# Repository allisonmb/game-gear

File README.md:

# Production Release - Game Gear
Our project was focused on recreating the original experience of the SEGA Game Gear handheld console with modern hardware and improved functionality.

[Build Instructions](Build%20Instructions.pdf)

[Bill of Materials](Bill%20of%20Materials.pdf)

[Raspberry Pi Image](https://drive.google.com/drive/u/0/folders/1cTOPLiqQtfveVBptVOEDtFShPZntb5K-)

Each aspect of the project is linked below, with README files indicating their functionality, how to run them, and known bugs.
- [Emulator ROM Implementation](romDev/)
- [Cartridge Auto Launch Scripts](romDev/udev_scripts/)
- [PCB Designs](https://github.com/allisonmb/game-gear/tree/17-pcb/pcbDesign)
- [GPIOnext](https://github.com/mholgatem/GPIOnext) - Used for interfacing with buttons through GPIO
- [3D Model](https://drive.google.com/file/d/1HNF1D_YHym1qWQATkMjLh69oOEiKL8Yn/view?usp=sharing) - Will need blender to view

Below are links to parts of the project that are no longer in development
- [FPGA Implementation](A-Z80/)
- [Z80 Assembly Test Code](<z80 assembly/>)

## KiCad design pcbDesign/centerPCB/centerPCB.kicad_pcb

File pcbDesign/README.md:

# PCB Design and Schematics
There are 3 PCBs: the left, right, and center PCBs. These are connected to eachother with header pins. Note: The "main PCB" is an old version which was before the PCB was split into 3. "GG PCB" is a remake of the original Game Gear PCB from https://oshwlab.com/maarten040476_3348/sega-game-gear-837-7996.
## Currently Implemented
### Center PCB
The center PCB connects to the left and right PCBs. 
The center PCB contains:
- [Raspberry Pi Zero W](https://www.raspberrypi.com/products/raspberry-pi-zero-w/)
- [3.5 Waveshare HDMI Screen](https://www.waveshare.com/wiki/3.5inch_HDMI_LCD)

### Left PCB
The left PCB contains:
- D-Pad buttons - These are traces on the board that are not connected. They are connected by a metal disk attached to the button that completes the circuit when the button is pushed.
- Power LED - A 3mm red LED with a 270 ohm resistor.

### Right PCB
The right PCB contains:
 - Start, 1, and 2 buttons - Works the same as the D-Pad buttons

## To be Implemented
### Center PCB
- Batery PCB - Need to decide on exact battery and battery board that will provide enough power for the other components

### Left PCB
- Volume Dial - Connected to rotary encoder that can be interpreted by the Raspberry Pi to change the system's volume level.
- Audio Amplifier - Connected to the Raspberry Pi and is capable of converting digital sound to anologue to go to a speaker. Currently looking at using [MAX98357A](https://www.adafruit.com/product/3006)

### Right PCB
The right PCB contains:
 - Brightness Dial - Same implementation as the volume dial, except for the screen brightness

## Current Issues
- The PCB is not complete, the parts listed above need to be added
- There may be an issue with using the MAX98357 audio amplifier with the PiJuice. Both use i2c for communication with the Raspberry Pi. However, they use different pins to do so and thus both may work together.
- The battery must be large enough to support the Raspberry Pi and the HDMI screen. The power consumption for both needs to be measured to choose a big enough battery.
- The largest single cell battery that can fit in the current case is 1200mAh. It is unlikely this is sufficient to power the console. There are two possible fixes for this. The case can be altered to allow a larger signle cell battery to fit, but this would cause issues with holding the console. Or multiple batteries in series could be used, but this would eliminate use of some battery PCBs which only work with single cell batteries.

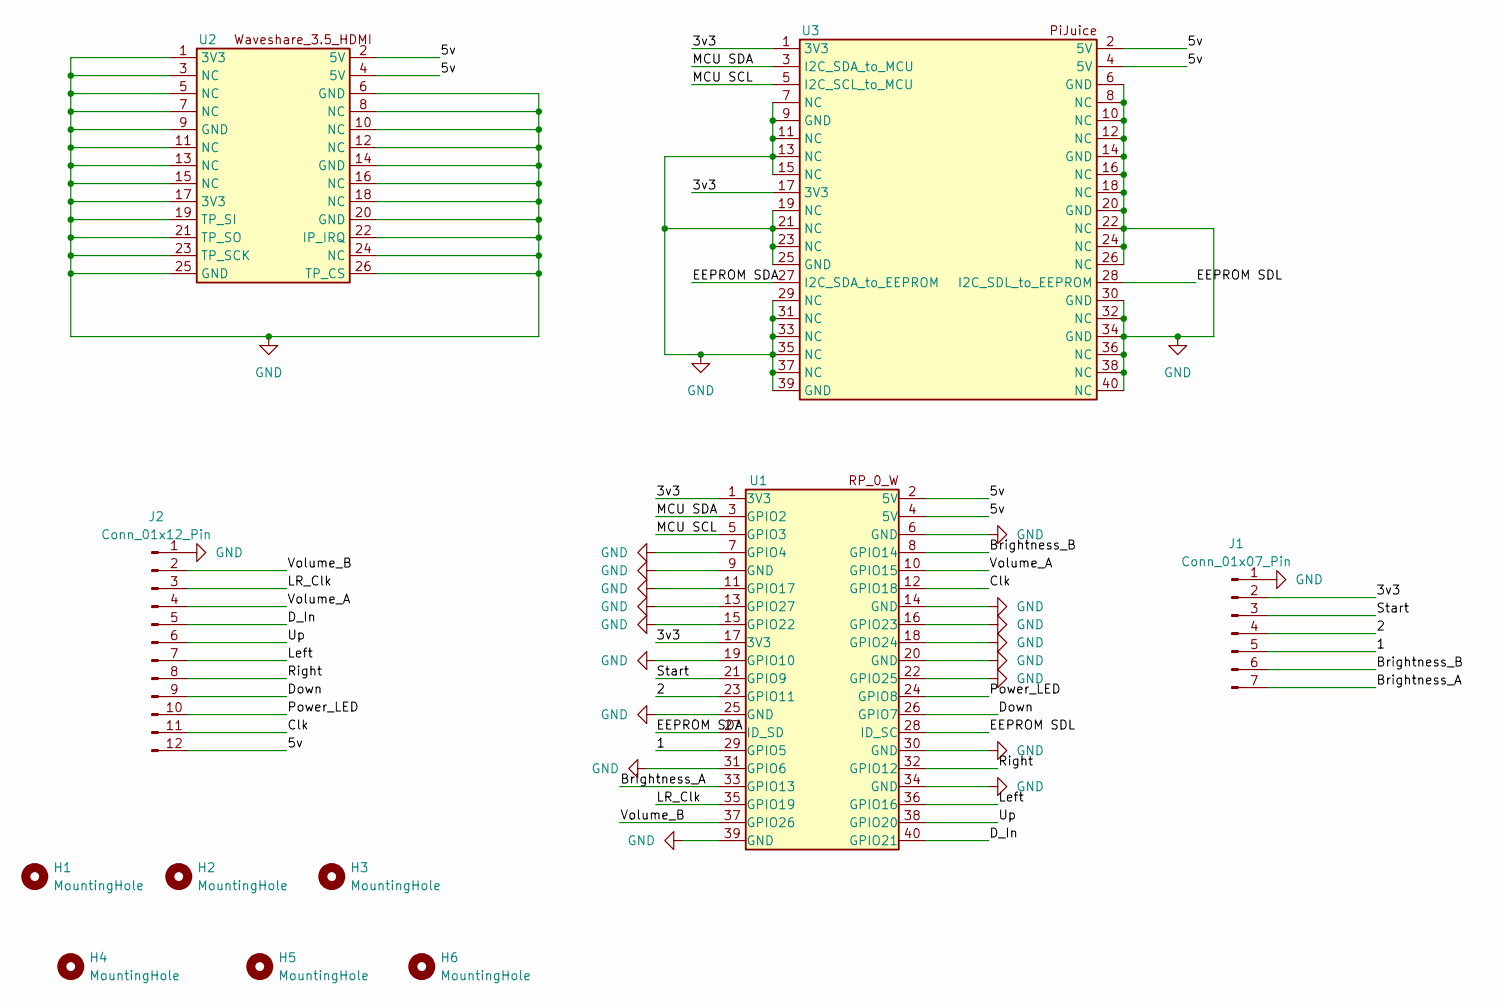
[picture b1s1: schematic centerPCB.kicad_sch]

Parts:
H1, H2, H3: MountingHole; MountingHole_2.1mm
H4, H5, H6: MountingHole; MountingHole_2.5mm
J1: Conn_01x07_Pin; PinHeader_1x07_P2.54mm_Vertical
J2: Conn_01x12_Pin; PinHeader_1x12_P2.54mm_Vertical
U1, U3: PinHeader_2x20_P2.54mm_Vertical
U2: PinHeader_2x13_P2.54mm_Vertical

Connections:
/1: J1.5, U1.29 (GPIO5)
/2: J1.4, U1.23 (GPIO11)
/3v3: J1.2, U1.1 (3V3), U1.17 (3V3), U3.1 (3V3), U3.17 (3V3)
/5v: J2.12, U1.2 (5V), U1.4 (5V), U2.2 (5V), U2.4 (5V), U3.2 (5V), U3.4 (5V)
/Brightness_A: J1.7, U1.33 (GPIO13)
/Brightness_B: J1.6, U1.8 (GPIO14)
/Clk: J2.11, U1.12 (GPIO18)
/D_In: J2.5, U1.40 (GPIO21)
/Down: J2.9, U1.26 (GPIO7)
/EEPROM SDA: U1.27 (ID_SD), U3.27 (I2C_SDA_to_EEPROM)
/EEPROM SDL: U1.28 (ID_SC), U3.28 (I2C_SDL_to_EEPROM)
/LR_Clk: J2.3, U1.35 (GPIO19)
/Left: J2.7, U1.36 (GPIO16)
/MCU SCL: U1.5 (GPIO3), U3.5 (I2C_SCL_to_MCU)
/MCU SDA: U1.3 (GPIO2), U3.3 (I2C_SDA_to_MCU)
/Power_LED: J2.10, U1.24 (GPIO8)
/Right: J2.8, U1.32 (GPIO12)
/Start: J1.3, U1.21 (GPIO9)
/Up: J2.6, U1.38 (GPIO20)
/Volume_A: J2.4, U1.10 (GPIO15)
/Volume_B: J2.2, U1.37 (GPIO26)
GND: J1.1, J2.1, U1.6 (GND), U1.7 (GPIO4), U1.9 (GND), U1.11 (GPIO17), U1.13 (GPIO27), U1.14 (GND), U1.15 (GPIO22), U1.16 (GPIO23), U1.18 (GPIO24), U1.19 (GPIO10), U1.20 (GND), U1.22 (GPIO25), U1.25 (GND), U1.30 (GND), U1.31 (GPIO6), U1.34 (GND), U1.39 (GND), U2.1 (3V3), U2.3 (NC), U2.5 (NC), U2.6 (GND), U2.7 (NC), U2.8 (NC), U2.9 (GND), U2.10 (NC), U2.11 (NC), U2.12 (NC), U2.13 (NC), U2.14 (GND), U2.15 (NC), U2.16 (NC), U2.17 (3V3), U2.18 (NC), U2.19 (TP_SI), U2.20 (GND), U2.21 (TP_SO), U2.22 (IP_IRQ), U2.23 (TP_SCK), U2.24 (NC), U2.25 (GND), U2.26 (TP_CS), U3.6 (GND), U3.7 (NC), U3.8 (NC), U3.9 (GND), U3.10 (NC), U3.11 (NC), U3.12 (NC), U3.13 (NC), U3.14 (GND), U3.15 (NC), U3.16 (NC), U3.18 (NC), U3.19 (NC), U3.20 (GND), U3.21 (NC), U3.22 (NC), U3.23 (NC), U3.24 (NC), U3.25 (GND), U3.26 (NC), U3.29 (NC), U3.30 (GND), U3.31 (NC), U3.32 (NC), U3.33 (NC), U3.34 (GND), U3.35 (NC), U3.36 (NC), U3.37 (NC), U3.38 (NC), U3.39 (GND), U3.40 (NC)

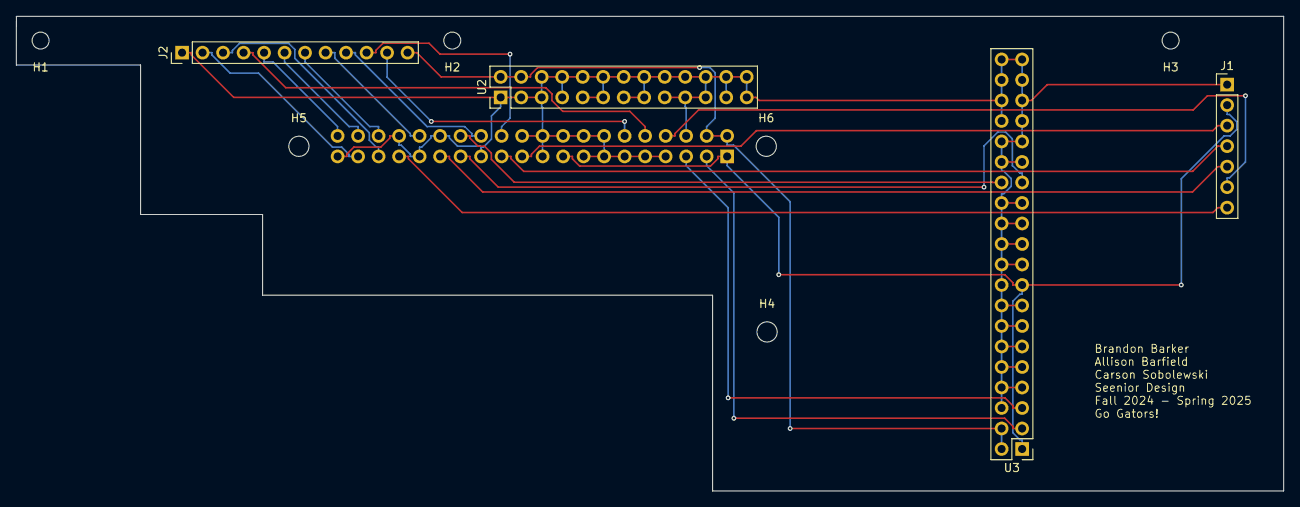
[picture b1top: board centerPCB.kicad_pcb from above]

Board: 2 copper layers, 157.0 x 58.8 mm, 11 parts (1 on the bottom side), 22 nets.

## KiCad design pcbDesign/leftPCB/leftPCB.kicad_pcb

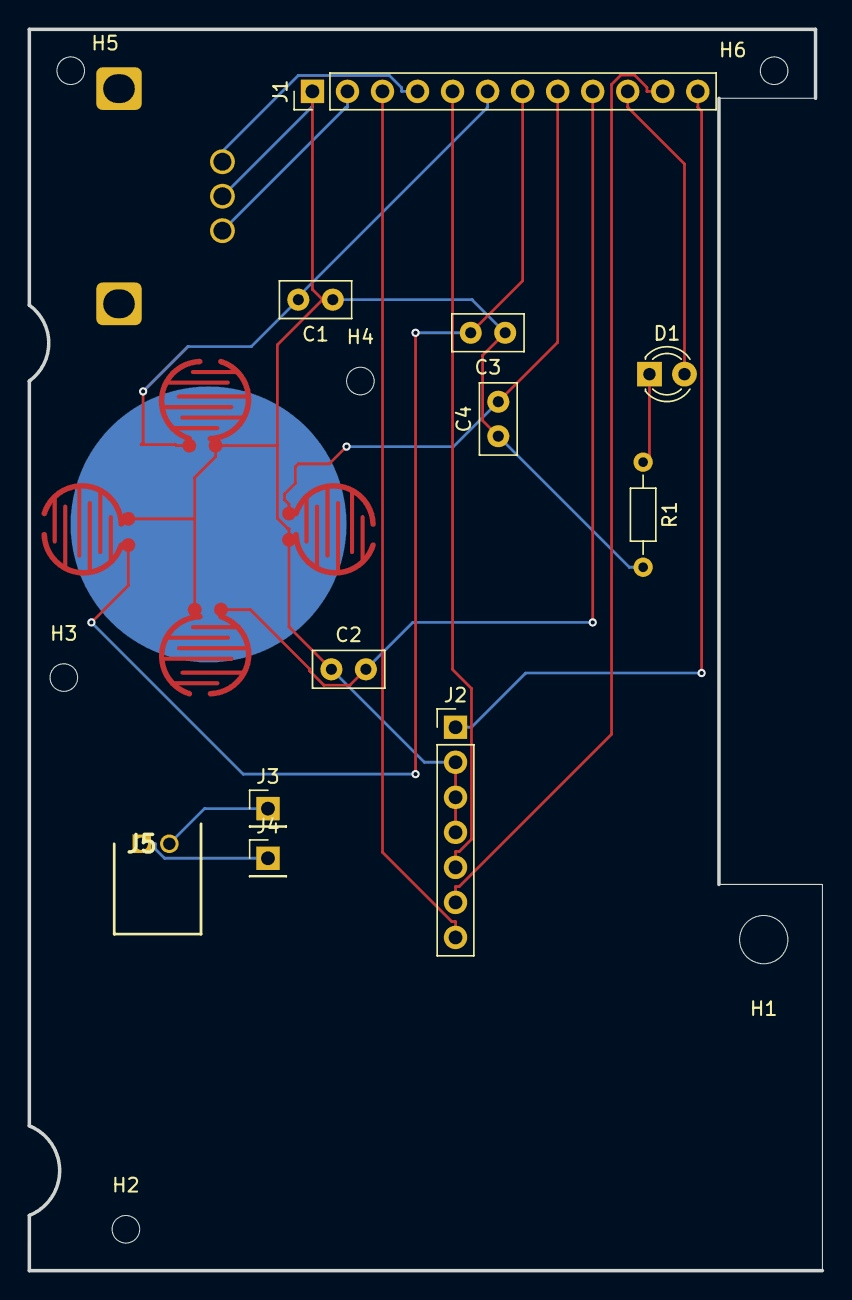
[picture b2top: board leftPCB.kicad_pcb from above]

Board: 2 copper layers, 57.5 x 90.0 mm, 22 parts (1 on the bottom side), 15 nets.

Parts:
C1, C2, C3, C4: 1u; C_Disc_D5.0mm_W2.5mm_P2.50mm
D1: LED; LED_D3.0mm
H1: MountingHole; MountingHole_3.5mm
H2, H3, H4, H5, H6: MountingHole; MountingHole_2mm
J1: Conn_01x12_Pin; PinHeader_1x12_P2.54mm_Vertical
J2: Conn_01x07_Pin; PinHeader_1x07_P2.54mm_Vertical
J3, J4: Conn_01x01_Pin; PinHeader_1x01_P2.54mm_Vertical
J5: 440055-2; SHDRRA2W50P0X200_1X2_600X770X525P
R1: R; R_Axial_DIN0204_L3.6mm_D1.6mm_P7.62mm_Horizontal
SW1: UP; BUTTON
SW2: DOWN; BUTTON
SW3: LEFT; BUTTON
SW4: RIGHT; BUTTON
SW5: RotaryEncoder; PES12

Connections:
/5v: J1.12, J2.1
/Clk: J1.11, J2.6
/D_In: J1.5, J2.5
/Down: C2.2, J1.9, SW2.2
/LR_Clk: J1.3, J2.7
/Left: C3.2, J1.7, SW3.2
/Power_LED: D1.2 (A), J1.10
/Right: C4.2, J1.8, SW4.2
/Speaker_Neg: J4.1, J5.1
/Speaker_Pos: J3.1, J5.2
/Up: C1.2, J1.6, SW1.2
/Volume_A: J1.4, SW5.A
/Volume_B: J1.2, SW5.B
GND: C1.1, C2.1, C3.1, C4.1, J1.1, J2.2, J2.3, J2.4, R1.2, SW1.1, SW2.1, SW3.1, SW4.1, SW5.C
unnamed: D1.1 (K), R1.1

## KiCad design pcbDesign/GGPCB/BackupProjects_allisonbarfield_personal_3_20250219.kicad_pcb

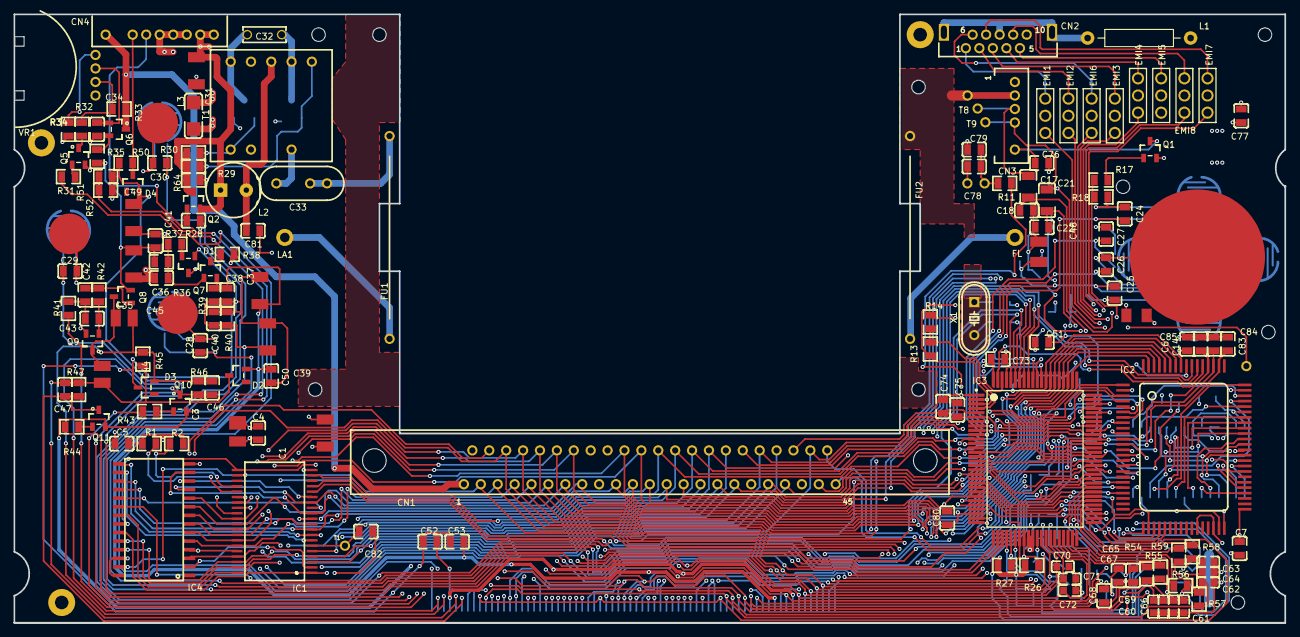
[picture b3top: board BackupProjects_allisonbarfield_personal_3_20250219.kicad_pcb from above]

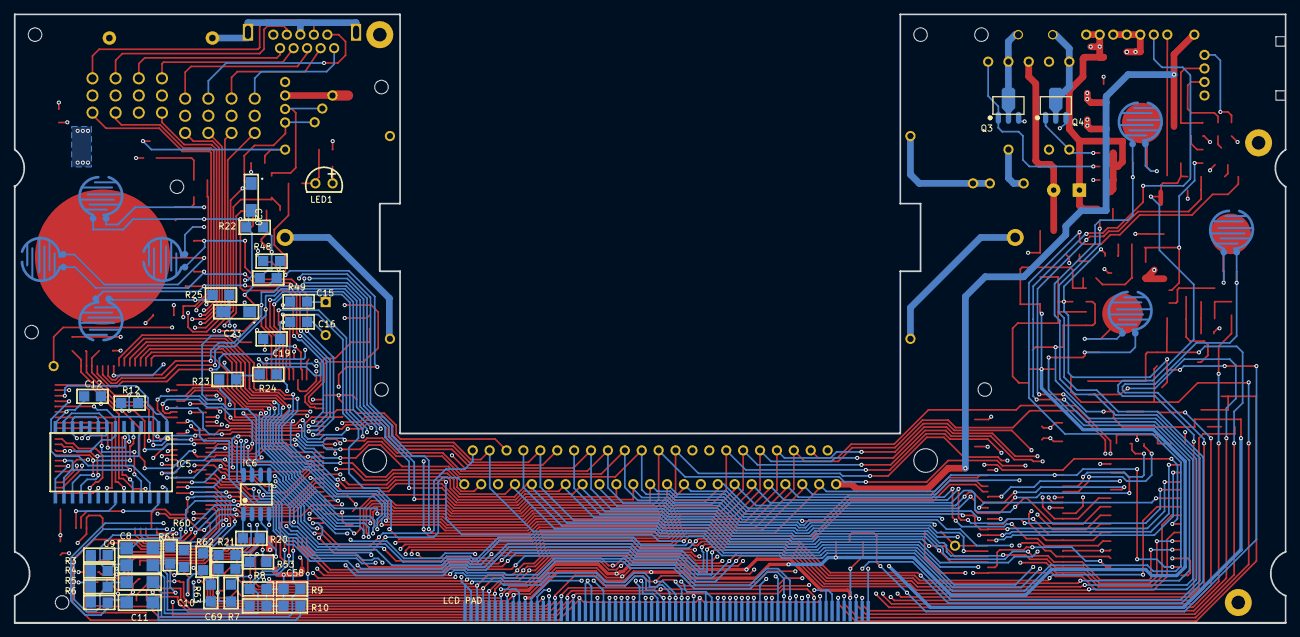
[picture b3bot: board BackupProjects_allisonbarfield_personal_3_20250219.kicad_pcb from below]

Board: 4 copper layers, 188.0 x 90.0 mm, 208 parts (47 on the bottom side), 196 nets.

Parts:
C1, C3, C6, C31, C35, C37, C39, C44, C45, C48, C49: 1u; CAPASITOR TEST
C4, C5, C7, C14, C18, C22, C24, C25, C26, C27, C28, C29, C30, C34, C36, C38, C40, C41, C42, C43, C46, C47, C50, C51, C52, C53, C65, C67, C68, C73, C74, C75, C76, C77, C78, C79, C80, C81, C82, C83, C84, C85: 1u; C0805
C8, C9, C10, C11: 1u; 1806
C12, C15, C16, C19, C58, C69: 1u; C1205
C17, C21: 1u; C1206
C20, C23: 1u; C20,23
C32: 1u; CERAMIC-5.08
C33: 1u; CAP33
C59, C60, C61, C62, C63, C64, C66, C70, C71, C72: 1u; C0603
CN1: CONN 45P FOR GG 01; CN1
CN2: CONN 10P FOR GG; CN2
CN3: WIRE HARN SP FOR GG; CONNECTOR3
CN4: CN4
D1, D2, D4: 1SS184; SOT-23-3_L2.9-W1.3-P1.90-LS2.4-TR
D3: 1SS184; TO-236MOD_L2.9-W1.5-P0.95-LS2.5-BR
EMI1, EMI2, EMI3, EMI4, EMI5, EMI6, EMI7, EMI8: EMI; FILTER-TH_3P-L8.0-W2.5-P2.54-R
FU1, FU2: Glass tube fuse2A 3F 250VAC; FUSE
Hole_gge24781: Hole_gge24781
Hole_gge24790: Hole_gge24790
Hole_gge24795: Hole_gge24795
Hole_gge24800: Hole_gge24800
Hole_gge24805: Hole_gge24805
Hole_gge24816: Hole_gge24816
Hole_gge24821: Hole_gge24821
Hole_gge24826: Hole_gge24826
Hole_gge24831: Hole_gge24831
IC1: TMPZ84C00AM-6; SSOP-40
IC2: 315-5377; 80-QFP
IC3: 315-5378B; 100QFP
IC4: MB8464A-10LL; FP-28DA
IC5: HM65256BLFP-10T; FP-28DA
IC6: IC6; KM 8SOP 5X6
L1: 1m; CHOKE_HORIZONTAL_RM15MM
L2: 1m; 100UH-3A
L3: 1m; L1806
LA1: Lamp; LAMP
LED1: LED; LED-TH_2P-L4.80-W3.80-P2.54-L
Pad_gge24769: Pad_gge24769
Pad_gge24780: Pad_gge24780
Pad_gge24811: Pad_gge24811
Pad_gge85411: Pad_gge85411
Pad_gge90736: Pad_gge90736
Pad_gge109066: Pad_gge109066
Pad_gge109074: Pad_gge109074
Pad_gge109081: Pad_gge109081
Q1, Q7: 2SC1623; SOT-23-3_L2.9-W1.3-P1.90-LS2.4-TR
Q2: 2SC1623???; SOT-23-3_L2.9-W1.3-P1.90-LS2.4-TR
Q3, Q4: 2sd1614; SOT89-3L
Q5, Q6, Q9, Q11: 2SC1623; SOT-23-3_L2.9-W1.3-P1.90-LS2.4-L
Q8: 2SA812; SOT-23-3_L2.9-W1.3-P1.90-LS2.4-TR
Q10: 2SA812; SOT-23-3_L2.9-W1.3-P1.90-LS2.4-L
R1, R2, R11, R13, R14, R17, R18, R26, R27, R30, R31, R32, R33, R34, R35, R36, R37, R38, R39, R40, R41, R42, R43, R44, R45, R46, R47, R50, R51, R52, R54, R55, R56, R57, R58, R59, R64: 0; R0805
R3, R4, R5, R6, R7, R8, R9, R10, R12, R20, R21, R22, R23, R24, R25, R48, R49, R53, R60, R61, R62, R63: 0; R1205
R28, R29: 0; C0805
SW1: UP; BUTTON
SW2: DOWN; BUTTON
SW3: LEFT; BUTTON
SW4: RIGHT; BUTTON
SW5: TL; BUTTON
SW6: TR; BUTTON
SW7: PS; BUTTON
T1: Transformer T1; TR1
U1: LCD PAD; LCD
VR1: 20K; VR1
X1: 32.2159MHz; HC-49US_L11.5-W4.5-P4.88

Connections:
+2.5V: C48.1, R7.1, R8.1, R9.1, R10.1, R26.1, R27.2, R48.2, R49.1
+5V: C1.1, C3.1, C4.1, C5.1, C6.1, C7.1, C12.1, C14.1, C31.1, C51.1, C77.2, C78.2, C80.1, CN1.2, CN1.35, CN4.1, CN4.2, EMI5.1, IC1.11, IC2.2, IC2.12, IC2.41, IC3.2, IC3.24, IC3.29, IC3.52, IC3.79, IC4.26, IC4.28, IC5.28, L2.1, L3.1, LED1.1, Q2.1, Q2.3, R1.1, R2.1, R12.2, R29.1, R30.1, R38.2, R64.2, U1.10, U1.30, U1.50
+34V: CN1.1, CN4.9, Q6.1, R33.2
A0: CN1.12, IC1.30, IC2.69, IC3.99, IC4.10
A1: CN1.11, IC1.31, IC3.98, IC4.9
A2: CN1.10, IC1.32, IC3.97, IC4.8
A3: CN1.9, IC1.33, IC3.96, IC4.7
A4: CN1.8, IC1.34, IC3.95, IC4.6
A5: CN1.7, IC1.35, IC3.94, IC4.5
A6: CN1.6, IC1.36, IC2.70, IC3.93, IC4.4
A7: CN1.5, IC1.37, IC2.71, IC3.92, IC4.3
A8: CN1.31, IC1.38, IC3.91, IC4.25
A9: CN1.30, IC1.39, IC3.90, IC4.24
A10: CN1.25, IC1.40, IC3.89, IC4.21
A11: CN1.29, IC1.1, IC4.23
A12: CN1.4, IC1.2, IC4.2
A13: CN1.32, IC1.3
A14: CN1.33, IC1.4, IC2.3
A15: CN1.28, IC1.5, IC2.4
AD0: IC2.45, IC5.10, IC5.11
AD1: IC2.46, IC5.9, IC5.12
AD2: IC2.48, IC5.8, IC5.13
AD3: IC2.49, IC5.7, IC5.15
AD4: IC2.50, IC5.6, IC5.16
AD5: IC2.51, IC5.5, IC5.17
AD6: IC2.53, IC5.4, IC5.18
AD7: IC2.54, IC5.19
ANALOG+5V: C19.1, CN3.1, IC6.8, L3.2, R3.2, R4.2, R5.2, R6.2, R48.1
C8_1: C8.1, IC3.36, R7.2
C9_2: C9.2, IC2.14, R4.1
C10_2: C10.2, IC2.15, R5.1
C11_2: C11.2, IC2.16, R6.1
C17_1: C17.1, C18.1, R20.2, R21.2
C21_1: C21.1, C22.2, R23.2, R24.2
C23_2: C23.2, CN1.45, R25.2
C32_1: C32.1, Q4.2, T1.1
C32_2: C32.2, Q3.2, T1.4
C33_1: C33.1, T1.8
C42_2: C42.2, C43.2, R41.1
C44_1: C44.1, C47.2, D2.3, R45.2, R47.2, U1.64
C45_2: C45.2, C46.2, D3.2, R45.1, R46.2, U1.66
C46_1: C46.1, Q10.1, R46.1, U1.67
C73_1: C73.1, IC3.100
CCLK: C74.2, CN1.40, IC3.5
CL2: IC3.46, U1.9, U1.29, U1.49
CLA1: C64.2, R59.2, U1.15
CLA2: C66.2, R61.2, U1.35
CLA3: C68.2, R63.2, U1.55
CLB1: C63.2, R58.2, U1.14
CLB2: C65.2, R60.2, U1.34
CLB3: C67.2, R62.2, U1.54
CLK: C82.2, IC1.6, Pad_gge85411.3
CN3_3: C17.2, CN3.3, Pad_gge109074.6
CN3_4: C21.2, CN3.4, Pad_gge109081.7
CN3_5: C76.1, CN3.5, IC3.25, Q1.3
CN4_6: CN4.6, IC3.30
CN4_7: CN4.7, D4.3, R50.1
D0: CN1.13, IC1.14, IC2.73, IC3.88, IC4.11
D1: CN1.14, IC1.15, IC2.74, IC3.87, IC4.12
D01: C61.2, R56.2, U1.18, U1.38, U1.58
D2: CN1.15, IC1.12, IC2.75, IC3.86, IC4.13
D02: C59.2, R54.2, U1.16, U1.36, U1.56
D3: CN1.19, IC1.8, IC2.76, IC3.85, IC4.15
D03: C62.2, R57.2, U1.19, U1.39, U1.59
D4: CN1.20, IC1.7, IC2.77, IC3.84, IC4.16
D04: C60.2, R55.2, U1.17, U1.37, U1.57
D5: CN1.21, IC1.9, IC2.78, IC3.83, IC4.17
D6: CN1.22, IC1.10, IC2.79, IC3.82, IC4.18
D7: CN1.23, IC1.13, IC2.1, IC3.81, IC4.19
DB: C58.2, R53.2, U1.3, U1.23, U1.43
DOWN: C25.2, IC3.8, SW2.1
DW: IC3.51, U1.20, U1.40, U1.60
EMI1_1: EMI1.1, IC3.72
EMI1_3: CN2.1, EMI1.3
EMI2_1: EMI2.1, IC3.73
EMI2_3: CN2.2, EMI2.3
EMI3_1: EMI3.1, IC3.74
EMI3_3: CN2.3, EMI3.3
EMI4_1: EMI4.1, IC3.75
EMI4_3: CN2.4, EMI4.3
EMI5_3: CN2.5, EMI5.3
EMI6_1: EMI6.1, IC3.76
EMI6_3: CN2.6, EMI6.3
EMI7_1: EMI7.1, IC3.78
EMI7_3: CN2.7, EMI7.3
EMI8_1: EMI8.1, IC3.77
EMI8_3: CN2.9, EMI8.3
EXM1: CN1.34, IC2.6
EXM2: CN1.27, IC2.7
FU1_1: C33.2, FU1.1
FU1_2: FU1.2, LA1.2
GG: CN1.42, IC3.66, R12.1, R31.1
GND: C1.2, C3.2, C4.2, C5.2, C6.2, C7.2, C12.2, C14.2, C15.2, C16.2, C18.2, C19.2, C22.1, C24.1, C25.1, C26.1, C27.1, C28.1, C29.1, C30.1, C31.2, C34.1, C35.2, C36.1, C41.1, C48.2, C49.2, C51.2, C58.1, C59.1, C60.1, C61.1, C62.1, C63.1, C64.1, C65.1, C66.1, C67.1, C68.1, C69.1, C70.1, C71.1, C72.1, C73.2, C74.1, C75.1, C76.2, C77.1, C79.1, C80.2, C81.1, C82.1, C83.2, C84.2, C85.2, CN1.16, CN1.17, CN1.18, CN1.41, CN3.2, CN4.3, CN4.4, CN4.5, D1.3, EMI1.2, EMI2.2, EMI3.2, EMI4.2, EMI5.2, EMI6.2, EMI7.2, EMI8.2, FU2.1, IC1.29, IC2.11, IC2.25, IC2.35, IC2.38, IC2.52, IC2.59, IC2.63, IC3.1, IC3.19, IC3.28, IC3.39, IC3.40, IC3.53, IC3.80, IC4.14, IC5.3, IC5.14, IC6.4, L1.1, Pad_gge109066.5, Q1.1, Q3.3, Q4.3, Q5.2, Q9.2, R18.1, R22.1, R25.1, R34.1, R49.2, R52.2, R64.1, SW1.1, SW2.2, SW3.1, SW4.1, SW5.2, SW6.2, SW7.1, T1.2, U1.1, U1.2, U1.13, U1.21, U1.22, U1.33, U1.41, U1.42, U1.53, U1.61, U1.62, U1.68
IC1_24: IC1.24, R2.2
IC1_25: IC1.25, R1.2
IC1_26: CN1.39, IC1.26, IC2.64, IC3.26
IC2_17: IC2.17, IC3.14
IC2_18: IC2.18, IC3.15
IC2_19: IC2.19, IC3.16
IC2_20: IC2.20, IC3.17
IC2_21: IC2.21, IC3.18
IC2_26: IC2.26, IC3.20
IC2_27: IC2.27, IC3.21
IC2_28: IC2.28, IC3.22
IC2_29: IC2.29, IC3.23
IC4_20: IC2.8, IC4.20
IC5_1: IC2.62, IC5.1
IC5_2: IC2.60, IC5.2
IC5_20: IC2.44, IC5.20
IC5_21: IC2.57, IC5.21
IC5_22: IC2.40, IC5.22
IC5_23: IC2.58, IC5.23
IC5_24: IC2.56, IC5.24
IC5_25: IC2.55, IC5.25
IC5_26: IC2.61, IC5.26
IC5_27: IC2.39, IC5.27
IC6_3: IC3.38, IC6.3, R26.2
IC6_5: IC3.37, IC6.5, R27.1
INT: IC1.16, IC2.72
IORQ: C85.1, CN1.37, IC1.20, IC2.68, IC3.69
L1_2: CN2.8, L1.2
L2_2: C81.2, L2.2, T1.3
LA1_1: FU2.2, LA1.1
LCD: IC3.64, R17.1, R18.2, R28.1
LE: C26.2, IC3.9, SW3.2
LED1_2: C78.1, C79.2, LED1.2, R11.1
M1: CN1.36, IC1.27, IC3.68
MREQ: CN1.24, IC1.19, IC2.5
NMI: IC1.17, IC3.67
P1: C72.2, IC3.45, U1.7, U1.27, U1.47
P2: C70.2, IC3.43, U1.5, U1.25, U1.45
P3: C69.2, IC3.42, U1.4, U1.24, U1.44
P4: C71.2, IC3.44, U1.6, U1.26, U1.46
PS: C30.2, IC3.13, SW7.2
Q1_2: Q1.2, R17.2
Q2_2: Q2.2, R28.2
Q3_1: Q3.1, R29.2, T1.5
Q4_1: Q4.1, R30.2, T1.6
Q5_1: Q5.1, R32.1
Q6_2: Q6.2, R35.1
Q8_2: C42.1, Q8.2, R42.2
Q8_3: C44.2, C45.1, Q8.3, Q9.1
Q9_3: C43.1, Q9.3, R42.1
Q10_3: Q10.3, R43.1
Q11_3: Q11.3, R44.1
R3_1: C8.2, IC2.13, R3.1
R8_2: C9.1, IC3.35, R8.2
R9_2: C10.1, IC3.34, R9.2
R10_2: C11.1, IC3.33, R10.2
R11_2: IC3.27, R11.2
R13_2: IC3.4, R13.2, R14.2
R20_1: IC6.1, IC6.2, R20.1
R21_1: C20.1, R21.1
R22_2: C20.2, CN1.44, R22.2
R23_1: IC6.6, IC6.7, R23.1
R24_1: C23.1, R24.1
R31_2: Q5.3, R31.2
R35_2: C35.1, C41.2, Q8.1, R35.2, R36.2
R36_1: C36.2, Q7.2, R36.1, R37.2
R37_1: D1.1, R37.1
R38_1: Q7.3, R38.1
R39_2: C37.1, C38.2, C50.2, C53.2, D2.1, Q7.1, R39.2, U1.11, U1.31, U1.51
R40_1: C37.2, C38.1, C39.2, C40.1, C50.1, C52.1, C53.1, D1.2, D3.3, R40.1, U1.12, U1.32, U1.52
R40_2: C39.1, C40.2, C52.2, Q10.2, Q11.2, R39.1, R40.2, U1.8, U1.28, U1.48, U1.65
R41_2: IC3.62, R41.2
R43_2: IC3.61, R43.2
R44_2: IC3.60, R44.2
R47_1: C47.1, Q11.1, R47.1, U1.63
R51_1: C49.1, D4.1, IC3.32, R50.2, R51.1
R52_1: IC3.31, R51.2, R52.1
R53_1: IC3.41, R53.1
R58_1: IC3.54, R58.1
R59_1: IC3.55, R59.1
R60_1: IC3.56, R60.1
R61_1: IC3.57, R61.1
R62_1: IC3.58, R62.1
R63_1: IC3.59, R63.1
RD: C83.1, CN1.26, IC1.21, IC2.66, IC3.71, IC4.22
RFSH: CN1.38, IC1.28
RI: C27.2, IC3.10, SW4.2
SAMP: IC3.63, Pad_gge90736.4
T3: IC3.49, R56.1
T4: IC3.47, R54.1
T5: IC3.50, R57.1
T6: IC3.48, R55.1
TL: C28.2, IC3.11, SW5.1
TR: C29.2, IC3.12, SW6.1
TV: CN1.43, IC3.65
UP: C24.2, IC3.7, SW1.2
VCLK: C75.2, IC2.10, IC3.6
VR1_1: R34.2, VR1.1
VR1_2: C34.2, Q6.3, VR1.2
VR1_3: R32.2, R33.1, VR1.3
WR: C84.1, CN1.3, IC1.22, IC2.67, IC3.70, IC4.27
X1_1: C15.1, IC3.3, R13.1, X1.1
X1_2: C16.1, R14.1, X1.2

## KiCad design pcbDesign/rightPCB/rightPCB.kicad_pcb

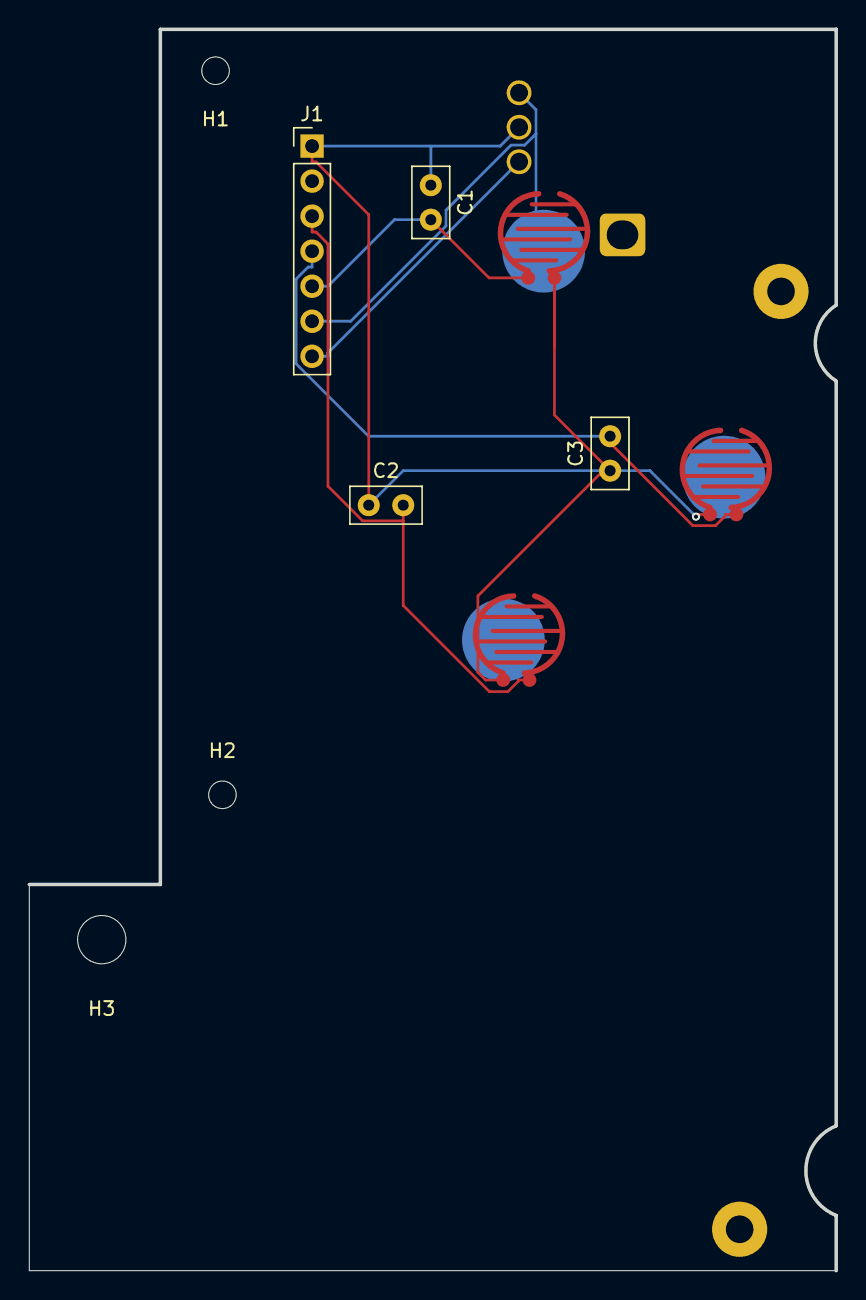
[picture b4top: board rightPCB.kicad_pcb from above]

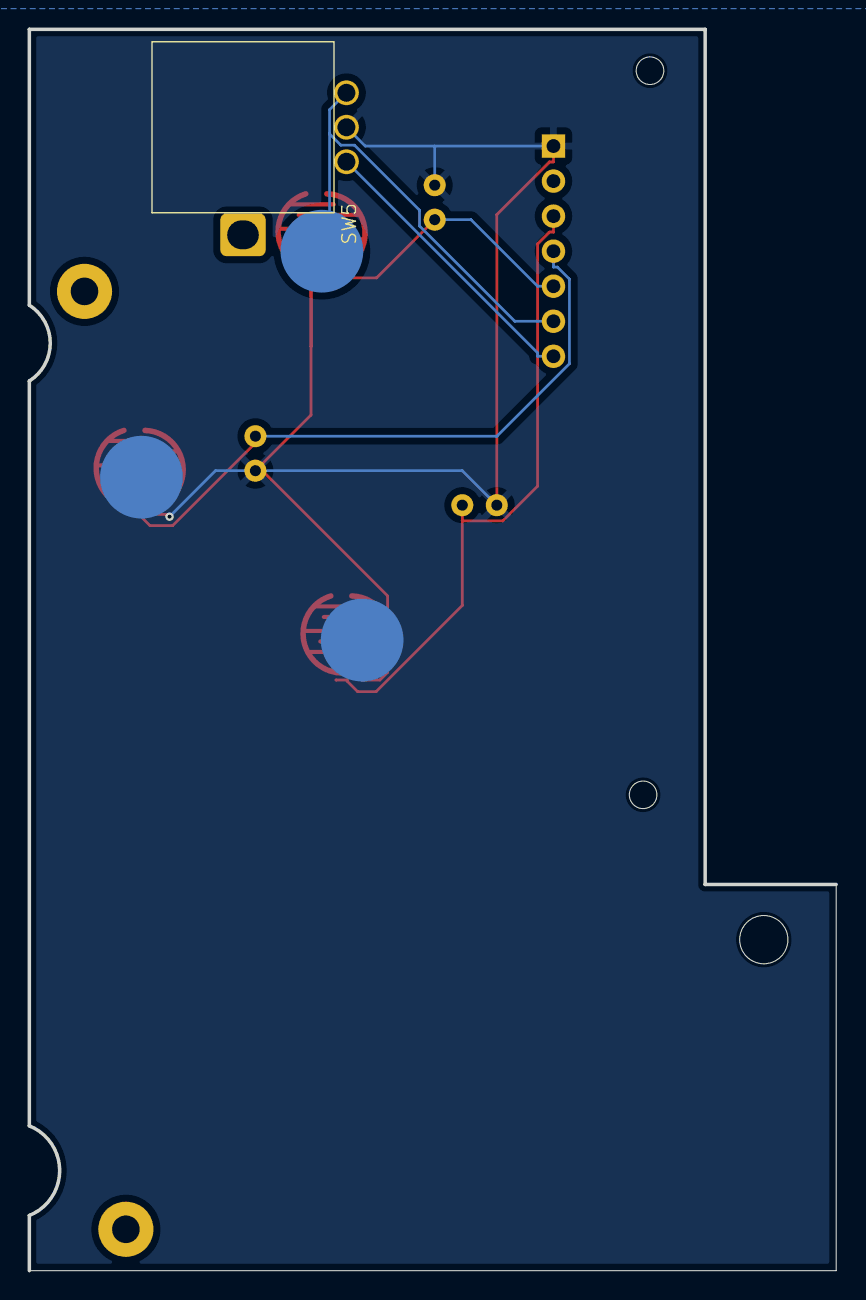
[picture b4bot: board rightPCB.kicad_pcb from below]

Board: 2 copper layers, 58.5 x 90.0 mm, 13 parts (3 on the bottom side), 6 nets.

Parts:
C1, C2, C3: 1u; C_Disc_D5.0mm_W2.5mm_P2.50mm
H1, H2: MountingHole; MountingHole_2mm
H3: MountingHole; MountingHole_3.5mm
J1: Conn_01x07_Pin; PinHeader_1x07_P2.54mm_Vertical
Pad_gge24769: Pad_gge24769
Pad_gge24780: Pad_gge24780
SW5: RotaryEncoder; PES12
SW6: TL; BUTTON
SW7: TR; BUTTON
SW8: PS; BUTTON

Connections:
/1: C2.2, J1.3, SW6.1
/2: C3.2, J1.4, SW7.1
/Brightness_A: J1.7, SW5.A
/Brightness_B: J1.6, SW5.B
/Start: C1.2, J1.5, SW8.2
GND: C1.1, C2.1, C3.1, J1.1, SW5.C, SW6.2, SW7.2, SW8.1

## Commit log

2024-10-24 Code for Sound Chip Emulation
    SN776489.ino is an arduino emulation of the sound chip as used in the Sega Game Gear
    Since the Arduino has no DAC, I chose to plot the output instead. It can be viewed in the Arduino serial window, or the Python script can be used to read the serial output and put it into a CSV to be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
2024-10-25 Using schematic from bit-preserve repo. Fixed some errors in it and replaced original IC3 chip with HM62256LP-15
2024-10-25 Added images for README
2024-10-25 Added images to README.md
2024-10-25 Added captions for images in README.md
2024-10-25 Z80 Verilog Files
2024-10-25 Added sound section, added references, and fixed screen resolution README.md
2024-10-25 Fixed references formatting README.md
2024-10-25 Fixed reference placement for image README.md
2024-10-26 Fixed sound chip number README.md
2024-12-01 updates to back board pcb
2024-12-01 Added testing file and basic instructions to use the ide
2024-12-01 Add demo project and add outline for asm
2024-12-01 Added arithmetic instructions to demo
2024-12-01 Added shift, rotate, and set instructions
2024-12-01 Added jump instructions
2024-12-02 Created a "Hello World" ROM in the .gg file format to be run on any Game Gear emulator
2024-12-02 Updated ReadMe to include info about the ROM
2024-12-02 Moved location of "Emulator Work" in Readme
2024-12-02 finished demo asm
2024-12-06 Updated movement and included code for button implementation on an Arduino
2024-12-06 Z80 Implementation (Hello World)
2024-12-06 Z80 Implementation FPGA
2024-12-07 Rename DesignPrototypeReadme.md to README.md
2024-12-07 Created Readme for ROM development and added Arduino files
2024-12-07 added car game and organized directory structure
2024-12-07 Update README.md
    Mentioned code compilation
2024-12-07 Create test
2025-02-01 Added schematic for custom controller
2025-02-20 Added schematic and pcb for original game gear main PCB and started designing schematic and pcb for the project's main pcb
2025-02-21 fixed error in pcb border
2025-02-23 udev scripts added
2025-02-24 Finalized pcb outline. There are now 3 pcbs instead of 1 to allow all components to fit. Also added some components.
2025-02-24 added README for udev
2025-02-24 Fix main README
2025-03-04 Updated pcbs and added footprint for rotary encoder (in progress)
2025-03-04 finalized center pcb component placement
2025-03-05 fixed
2025-03-05 routed centerpcb
2025-03-05 Updated left header pins
2025-03-05 Updated traces
2025-03-06 Updated PCB designs for left and right boards
2025-03-06 Routed
2025-03-06 Finalized placement on left pcb
2025-03-06 Edited PCB for rotary encoder
2025-03-06 Finalized center and left pcbs placemnt
2025-03-06 right pcb edits
2025-03-06 saved schematic
2025-03-07 rerouted
2025-03-07 Added names on silk layer
2025-03-29 added piJuice readme
2025-04-11 Adding lowPowerLED script
2025-04-13 Update lowPowerLED.py
    Re Enabled PiJuice charge % reading
2025-04-14 Fixed overlapping boards issues by cutting out areas in design Rerouted dpad traces to not interfere with each other Added "filesForOrder"
2025-04-15 Documents
